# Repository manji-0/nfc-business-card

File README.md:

# NFC Business Card (KiCad → JLCPCB)

Passive NFC PCB business card: **89 × 51 mm**, URL NDEF, rewritable from iPhone.

| Item | Value |
|------|-------|
| IC | NXP **NT3H2111W0FHKH** (Type 2 / NTAG I²C plus) |
| LCSC | **C710403** (JLCPCB Extended, SMT) |
| Board | 2-layer, **0.8 mm**, **black** mask, white silk, ENIG |
| Antenna | Right zone ~29 × 45 mm, **5 turns**, 0.25 / 0.30 mm |
| Text zone | Left **50 mm** — name as **ENIG copper**; roles / QR / contacts in silk |
| Components | 7 mm strip between text and antenna (U1 + C1 DNP) |

## Repo layout

```
nfc-business-card.kicad_*   KiCad project
lib/                        Symbols & footprints
antenna/                    Design notes + spiral points
fab/                        Gerber zip, BOM, CPL, preview, gerber/
scripts/                    Regenerate project / fab
parts.md                    Locked BOM
```

## Setup (from scratch)

Use **[devbox](https://www.jetify.com/devbox)** + **[uv](https://docs.astral.sh/uv/)** for Python and tooling. KiCad 10+ is installed separately.

```bash
git clone https://github.com/manji-0/nfc-business-card.git
cd nfc-business-card
devbox shell          # installs python, uv, rsvg-convert; runs uv sync
./task export
```

Full guide: **[SETUP.md](SETUP.md)** (fonts, KiCad path, troubleshooting).

## Regenerate design

```bash
./task export          # full pipeline: assets → KiCad → preview → check → fab
./task design          # design only (no Gerber export)
./task list            # show all tasks
```

Individual steps: `./task assets project preview fab` (runs in order).

Open `nfc-business-card.kicad_pro` in KiCad 8+ to edit silk text, tweak antenna, or re-export with **JLCPCB Fabrication Toolkit**.

Photoreal mockup (front + back, regenerated by `./task preview`):

```bash
./task preview
```

Front NFC icon: `assets/nfc-symbol.svg` (from SVG Repo). Check license/terms if you ship commercially.

## Order on JLCPCB

Follow [`fab/ORDER_CHECKLIST.md`](fab/ORDER_CHECKLIST.md).

1. Upload `fab/nfc-business-card-gerbers.zip` (or KiCad Toolkit output).
2. Enable SMT Assembly; upload `fab/bom.csv` + `fab/positions.csv`.
3. Confirm U1 = C710403 and rotation in the preview.
4. First run: **5 boards**.

## Write / rewrite URL (iPhone & Android)

1. Install **NFC Tools** (or NXP TagWriter).
2. Write → Add record → **URL / URI** → your `https://…` page → Write.
3. Tap the card (iPhone: near the top/camera area on modern models).

### Rules for rewritability

- **Do not** use “Lock”, “Make read-only”, or OTP lock. That is permanent.
- Optional: enable **write password only** (PROT = write protect). Reads still open the URL; rewriting needs the password in the same app session.
- After a successful write, lock the phone and tap again to confirm Safari/Chrome opens without an app.

## Design notes

See [`antenna/NOTES.md`](antenna/NOTES.md) and [`parts.md`](parts.md).

- Left **text zone**: name on **F.Cu** (mask opening + ENIG); roles, QR, contacts in silk.
- NFC antenna + chip sit on the **right** (reference-card style).
- If read range is weak, try C1 ≈ **10 pF NP0** first (LCSC **C301961**); then 12/15/18 pF per `parts.md`.

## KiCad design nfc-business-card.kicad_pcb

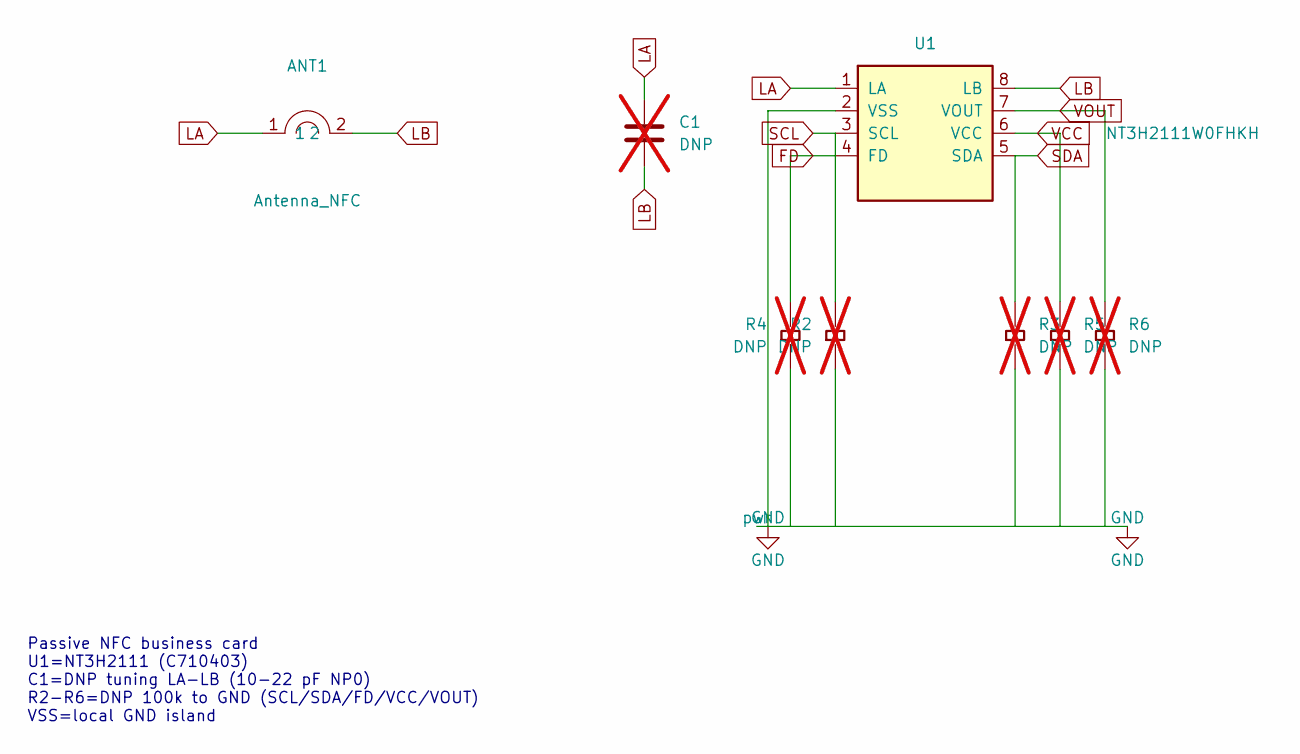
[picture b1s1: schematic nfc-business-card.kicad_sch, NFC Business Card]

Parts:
ANT1: Antenna_NFC; Antenna_Spiral_29x45_5T
C1: DNP; C_0402_1005Metric; LCSC Part # C301961; not fitted
R2, R3, R4, R5, R6: DNP; R_0402_1005Metric; LCSC Part # C60491; not fitted
U1: NT3H2111W0FHKH; XQFN-8_1.6x1.6mm_P0.4mm_NT3H2111; LCSC Part # C710403

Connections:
FD: R4.1, U1.4 (FD)
GND: R2.2, R3.2, R4.2, R5.2, R6.2, U1.2 (VSS); also elsewhere on the board
LA: ANT1.1, C1.1, U1.1 (LA)
LB: ANT1.2, C1.2, U1.8 (LB)
SCL: R2.1, U1.3 (SCL)
SDA: R3.1, U1.5 (SDA)
VCC: R5.1, U1.6 (VCC)
VOUT: R6.1, U1.7 (VOUT)

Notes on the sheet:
Passive NFC business card U1=NT3H2111 (C710403) C1=DNP tuning LA-LB (10-22 pF NP0) R2-R6=DNP 100k to GND (SCL/SDA/FD/VCC/VOUT) VSS=local GND island

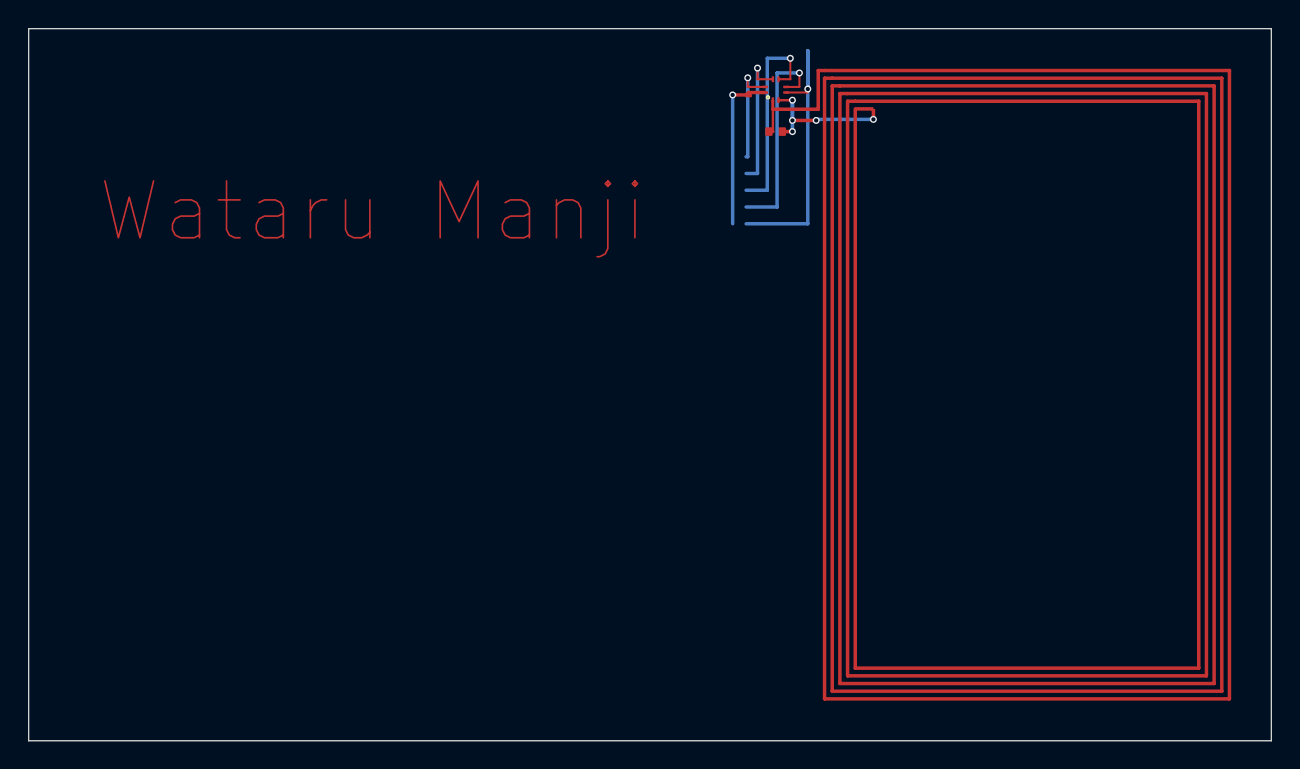
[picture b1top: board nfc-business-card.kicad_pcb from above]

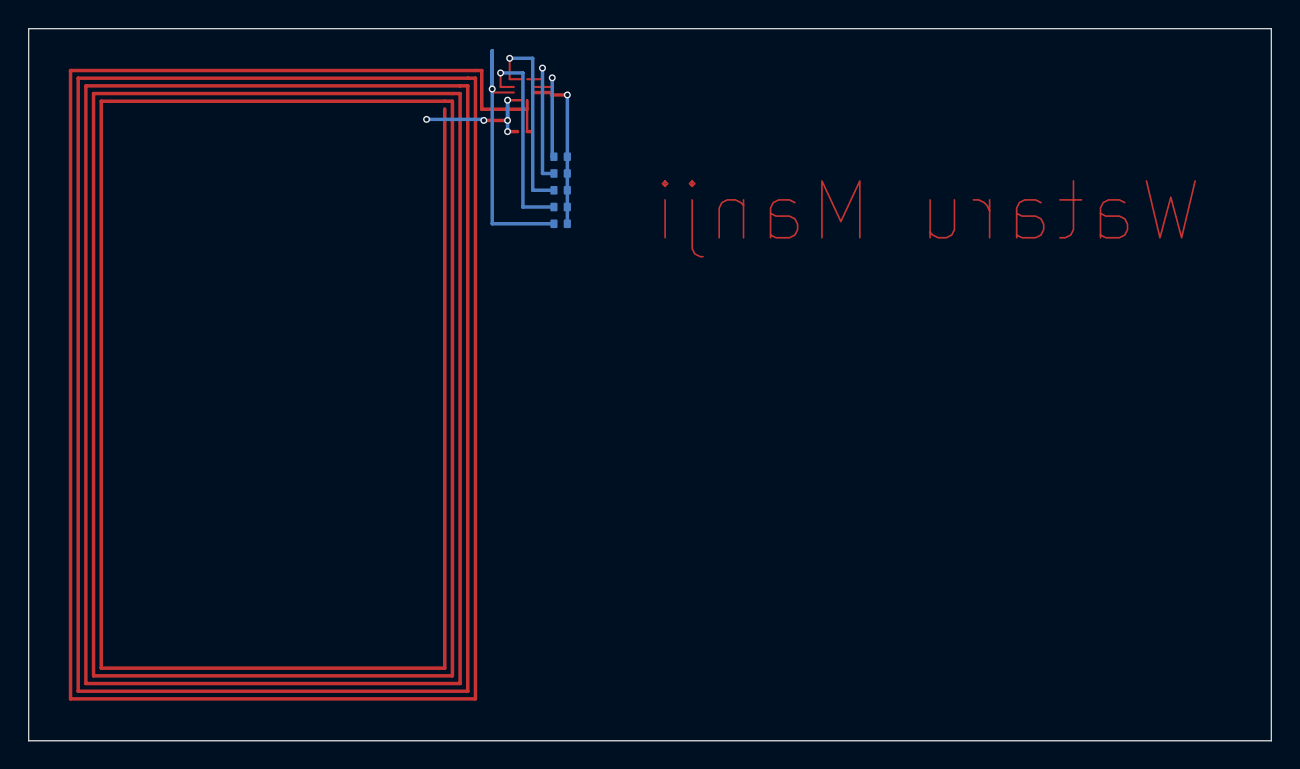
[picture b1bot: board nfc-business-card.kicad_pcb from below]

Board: 2 copper layers, 89.0 x 51.0 mm, 9 parts (5 on the bottom side), 8 nets.

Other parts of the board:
GND1: GND; GND_Island

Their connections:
GND: GND1.1; also elsewhere on the board
